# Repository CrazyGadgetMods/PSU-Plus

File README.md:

# PSU-Plus
The PSU-Plus is the spiritual successor to Noah's RVL-PSU, designed for ease of assembly and versatility across many micro-type builds.

Like it's predecessor, the PSU-Plus has 1V, 1.15V, 3.3V and 5V regulators. Where the PSU-Plus differs is the addition of a 1.8V regulator for builds that remove the LDO from the Wii (such as Wesk's GC Micro and the GC Nano).

I designed this board when the TLV62130RGTR regulators were out of stock as a drop-in replacement for the RVL-PSU. It has the exact same board outline dimensions, as well as the same screw hole layout / dimensions.

I have added an additional VIN pad for builds that use VIN elsewhere in the project (such as feeding 12V to the audio amplifier / sensor bar in the Noldendo Miicro). I have also added jumper pads to enable / disable the 1v8 and 5v regulars if your build does not require either of them.

**VIN Min: 5V**\
**VIN Max: 18V**\
**Max current output (per regulator): 3A**

If you are interested in buying one of these boards pre-assembled, I sell them on my [Etsy Store](https://www.etsy.com/listing/1510321427/psu-plus-power-board-for-wii-micros).

## Credits
- [YveltalGriffin](https://github.com/mackieks): Holding my hand while I did the layout of the board and answering my infinite questions
- [Noah](https://bitbuilt.net/forums/index.php?members/noah.1/): Making the original [RVL-PSU](https://bitbuilt.net/forums/index.php?threads/rvl-psu.3335/)
- [BitBuilt](https://bitbuilt.net/): Being the best modding community out there!

## License
Solderpad Hardware License v2.1

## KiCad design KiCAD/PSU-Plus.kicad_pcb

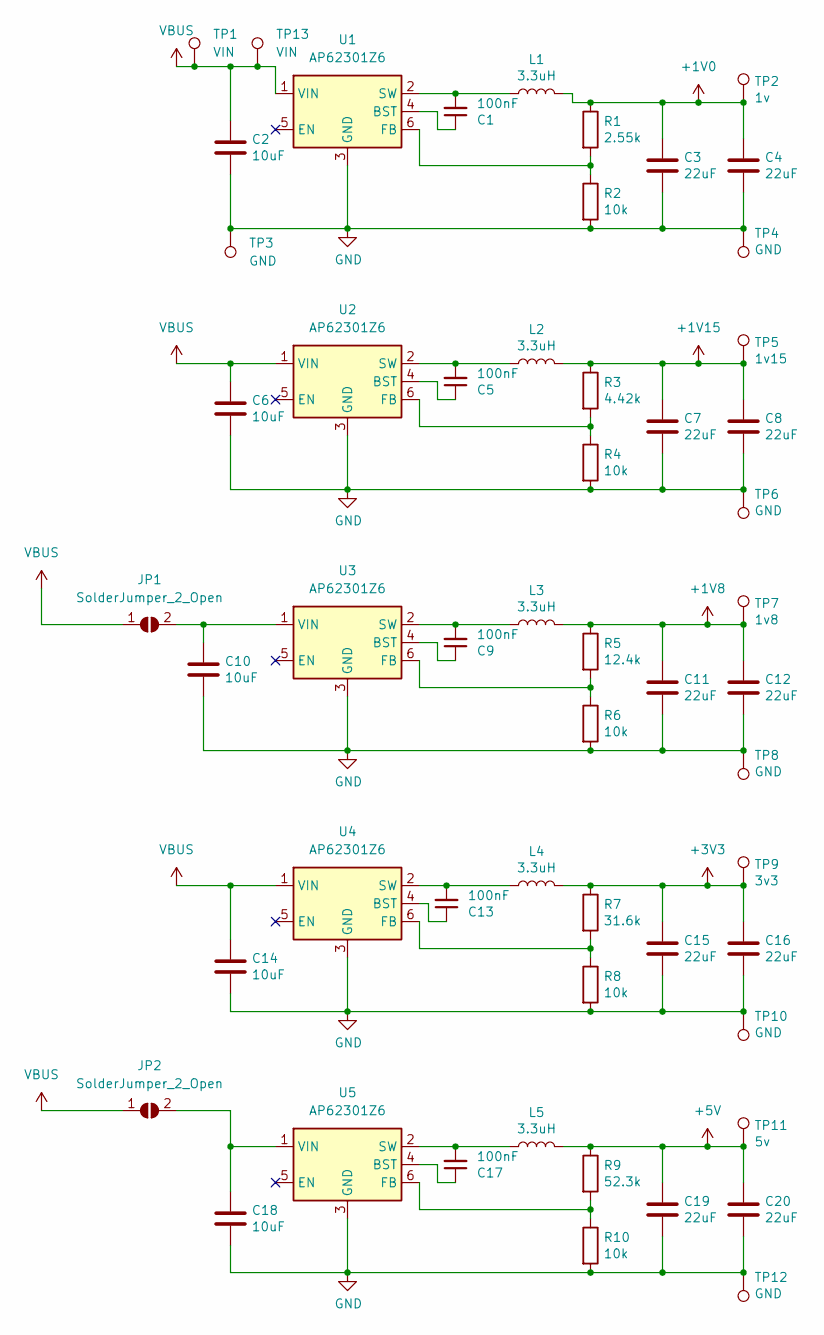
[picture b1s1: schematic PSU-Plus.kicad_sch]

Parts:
C1, C5, C9, C13, C17: 100nF; C_0402_1005Metric
C2, C6, C10, C14, C18: 10uF; C_0805_2012Metric
C3, C4, C7, C8, C11, C12, C15, C16, C19, C20: 22uF; C_0603_1608Metric
JP1, JP2: SolderJumper_2_Open; SolderJumper-2_P1.3mm_Open_Pad1.0x1.5mm
L1, L2, L3, L4, L5: 3.3uH; L_Chilisin_BMRx00050512-B
R1: 2.55k; R_0402_1005Metric
R2, R4, R6, R8, R10: 10k; R_0402_1005Metric
R3: 4.42k; R_0402_1005Metric
R5: 12.4k; R_0402_1005Metric
R7: 31.6k; R_0402_1005Metric
R9: 52.3k; R_0402_1005Metric
TP1, TP13: VIN; TestPoint_Pad_2.0x2.0mm
TP2: 1v; TestPoint_Pad_2.0x2.0mm
TP3, TP4, TP6, TP8, TP10, TP12: GND; TestPoint_Pad_2.0x2.0mm
TP5: 1v15; TestPoint_Pad_2.0x2.0mm
TP7: 1v8; TestPoint_Pad_2.0x2.0mm
TP9: 3v3; TestPoint_Pad_2.0x2.0mm
TP11: 5v; TestPoint_Pad_2.0x2.0mm
U1, U2, U3, U4, U5: AP62301Z6; SOT-563

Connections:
+1V0: C3.1, C4.1, L1.2, R1.1, TP2.1
+1V8: C11.1, C12.1, L3.2, R5.1, TP7.1
+1V15: C7.1, C8.1, L2.2, R3.1, TP5.1
+3V3: C15.1, C16.1, L4.2, R7.1, TP9.1
+5V: C19.1, C20.1, L5.2, R9.1, TP11.1
GND: C2.1, C3.2, C4.2, C6.1, C7.2, C8.2, C10.1, C11.2, C12.2, C14.1, C15.2, C16.2, C18.1, C19.2, C20.2, R2.2, R4.2, R6.2, R8.2, R10.2, TP3.1, TP4.1, TP6.1, TP8.1, TP10.1, TP12.1, U1.3 (GND), U2.3 (GND), U3.3 (GND), U4.3 (GND), U5.3 (GND)
unnamed: C10.2, JP1.2 (B), U3.1 (VIN)
unnamed: C18.2, JP2.2 (B), U5.1 (VIN)
unnamed: C1.1, U1.4 (BST)
unnamed: R1.2, R2.1, U1.6 (FB)
unnamed: C1.2, L1.1, U1.2 (SW)
unnamed: C5.1, U2.4 (BST)
unnamed: R3.2, R4.1, U2.6 (FB)
unnamed: C5.2, L2.1, U2.2 (SW)
unnamed: C9.1, U3.4 (BST)
unnamed: R5.2, R6.1, U3.6 (FB)
unnamed: C9.2, L3.1, U3.2 (SW)
unnamed: C13.1, U4.4 (BST)
unnamed: R7.2, R8.1, U4.6 (FB)
unnamed: C13.2, L4.1, U4.2 (SW)
unnamed: C17.1, U5.4 (BST)
unnamed: R9.2, R10.1, U5.6 (FB)
unnamed: C17.2, L5.1, U5.2 (SW)
VBUS: C2.2, C6.2, C14.2, JP1.1 (A), JP2.1 (A), TP1.1, TP13.1, U1.1 (VIN), U2.1 (VIN), U4.1 (VIN)

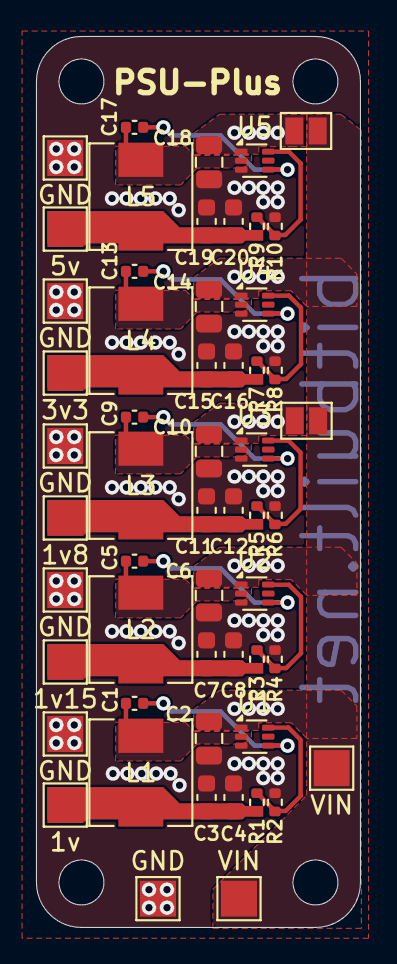
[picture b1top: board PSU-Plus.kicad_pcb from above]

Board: 2 copper layers, 18.0 x 49.5 mm, 55 parts (0 on the bottom side), 24 nets.

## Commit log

2024-05-08 init
2024-05-15 Schematic refreshing, redoing PCB layout, gerbers
